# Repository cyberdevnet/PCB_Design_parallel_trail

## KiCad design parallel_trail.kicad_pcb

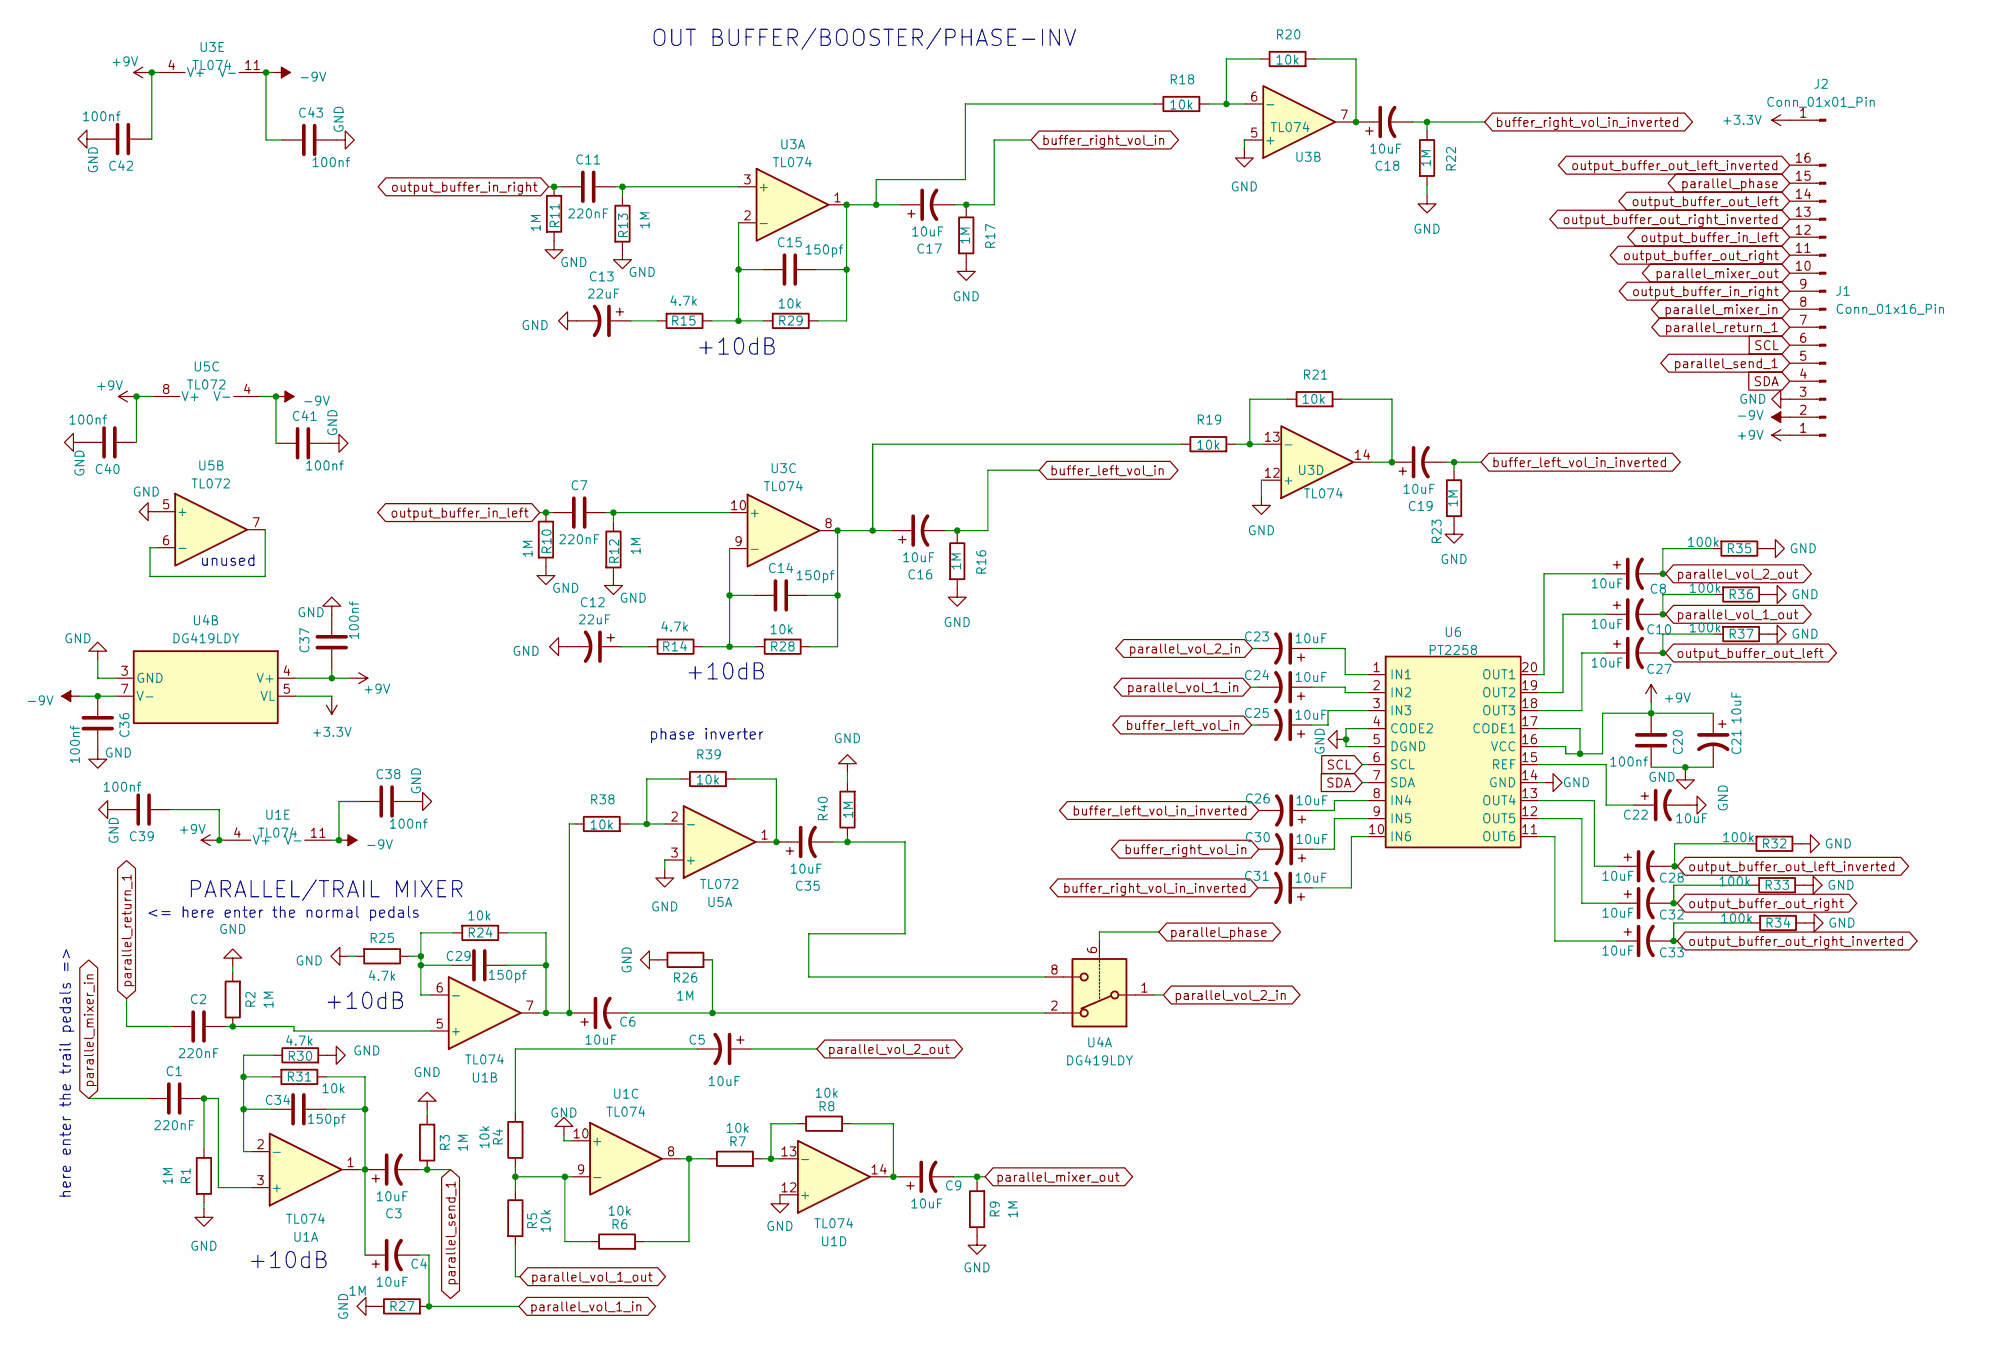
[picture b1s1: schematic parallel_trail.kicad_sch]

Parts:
C1, C2, C7, C11: 220nF; C_0805_2012Metric
C3, C4, C5, C6, C8, C9, C10, C16, C17, C18, C19, C21, C22, C23, C24, C25, C26, C27, C28, C30, C31, C32, C33, C35: 10uF; C_0805_2012Metric
C12, C13: 22uF; C_Elec_6.3x5.4
C14, C15, C29, C34: 150pf; C_0805_2012Metric
C20, C36, C37, C38, C39, C40, C41, C42, C43: 100nf; C_0805_2012Metric
J1: Conn_01x16_Pin; PinHeader_2x08_P2.54mm_Vertical
J2: Conn_01x01_Pin; PinHeader_1x01_P1.00mm_Vertical
R1, R2, R3, R9, R10, R11, R12, R13, R16, R17, R22, R23, R26, R27, R40: 1M; R_0805_2012Metric
R4, R5, R6, R7, R8, R18, R19, R20, R21, R24, R28, R29, R31, R38, R39: 10k; R_0805_2012Metric
R14, R15, R25, R30: 4.7k; R_0805_2012Metric
R32, R33, R34, R35, R36, R37: 100k; R_0805_2012Metric
U1, U3: TL074; SO-14_3.9x8.65mm_P1.27mm
U4: DG419LDY; SOIC-8_3.9x4.9mm_P1.27mm
U5: TL072; SO-8_3.9x4.9mm_P1.27mm
U6: PT2258; SOP-20_7.5x12.8mm_P1.27mm

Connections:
+3.3V: J2.1, U4.5 (VL)
+9V: C20.2, C21.1, C37.2, C39.2, C40.2, C42.2, J1.1, U1.4 (V+), U3.4 (V+), U4.4 (V+), U5.8 (V+), U6.16 (VCC), U6.17 (CODE1)
-9V: C36.2, C38.2, C41.2, C43.2, J1.2, U1.11 (V-), U3.11 (V-), U4.7 (V-), U5.4 (V-)
GND: C12.2, C13.2, C20.1, C21.2, C22.2, C36.1, C37.1, C38.1, C39.1, C40.1, C41.1, C42.1, C43.1, J1.3, R1.2, R2.2, R3.2, R9.1, R10.2, R11.2, R12.2, R13.2, R16.2, R17.2, R22.2, R23.2, R25.2, R26.1, R27.1, R30.2, R32.1, R33.1, R34.1, R35.1, R36.1, R37.1, R40.2, U1.10 (+), U1.12 (+), U3.5 (+), U3.12 (+), U4.3 (GND), U5.3 (+), U5.5 (+), U6.4 (CODE2), U6.5 (DGND), U6.14 (GND)
unnamed: C3.1, C4.1, C34.1, R31.1, U1.1
unnamed: C5.2, R4.2
unnamed: C6.2, R26.2, U4.2
unnamed: C9.1, R8.2, U1.14
unnamed: C12.1, R14.2
unnamed: C13.1, R15.2
unnamed: C14.1, C16.1, R19.1, R28.1, U3.8
unnamed: C15.1, C17.1, R18.1, R29.1, U3.1
unnamed: C18.1, R20.2, U3.7
unnamed: C19.1, R21.2, U3.14
unnamed: C6.1, C29.1, R24.1, R38.1, U1.7
unnamed: C35.1, R39.2, U5.1
unnamed: C35.2, R40.1, U4.8
unnamed: R6.2, R7.1, U1.8
unnamed: C1.1, R1.1, U1.3 (+)
unnamed: C34.2, R30.1, R31.2, U1.2 (-)
unnamed: C2.1, R2.1, U1.5 (+)
unnamed: C29.2, R24.2, R25.1, U1.6 (-)
unnamed: R4.1, R5.1, R6.1, U1.9 (-)
unnamed: R7.2, R8.1, U1.13 (-)
unnamed: C11.1, R13.1, U3.3 (+)
unnamed: C15.2, R15.1, R29.2, U3.2 (-)
unnamed: R18.2, R20.1, U3.6 (-)
unnamed: C7.1, R12.1, U3.10 (+)
unnamed: C14.2, R14.1, R28.2, U3.9 (-)
unnamed: R19.2, R21.1, U3.13 (-)
unnamed: R38.2, R39.1, U5.2 (-)
unnamed: U5.6 (-), U5.7
unnamed: C23.1, U6.1 (IN1)
unnamed: C24.1, U6.2 (IN2)
unnamed: C25.1, U6.3 (IN3)
unnamed: C26.1, U6.8 (IN4)
unnamed: C30.1, U6.9 (IN5)
unnamed: C31.1, U6.10 (IN6)
unnamed: C8.1, U6.20 (OUT1)
unnamed: C10.1, U6.19 (OUT2)
unnamed: C27.1, U6.18 (OUT3)
unnamed: C28.1, U6.13 (OUT4)
unnamed: C32.1, U6.12 (OUT5)
unnamed: C33.1, U6.11 (OUT6)
unnamed: C22.1, U6.15 (REF)
SCL: J1.6, U6.6 (SCL)
SDA: J1.4, U6.7 (SDA)
buffer_left_vol_in: C16.2, C25.2, R16.1
buffer_left_vol_in_inverted: C19.2, C26.2, R23.1
buffer_right_vol_in: C17.2, C30.2, R17.1
buffer_right_vol_in_inverted: C18.2, C31.2, R22.1
output_buffer_in_left: C7.2, J1.12, R10.1
output_buffer_in_right: C11.2, J1.9, R11.1
output_buffer_out_left: C27.2, J1.14, R37.2
output_buffer_out_left_inverted: C28.2, J1.16, R32.2
output_buffer_out_right: C32.2, J1.11, R33.2
output_buffer_out_right_inverted: C33.2, J1.13, R34.2
parallel_mixer_in: C1.2, J1.8
parallel_mixer_out: C9.2, J1.10, R9.2
parallel_phase: J1.15, U4.6
parallel_return_1: C2.2, J1.7
parallel_send_1: C3.2, J1.5, R3.1
parallel_vol_1_in: C4.2, C24.2, R27.2
parallel_vol_1_out: C10.2, R5.2, R36.2
parallel_vol_2_in: C23.2, U4.1
parallel_vol_2_out: C5.1, C8.2, R35.2

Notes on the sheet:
here enter the trail pedals =>
+10dB
unused
phase inverter
PARALLEL/TRAIL MIXER
<= here enter the normal pedals
OUT BUFFER/BOOSTER/PHASE-INV

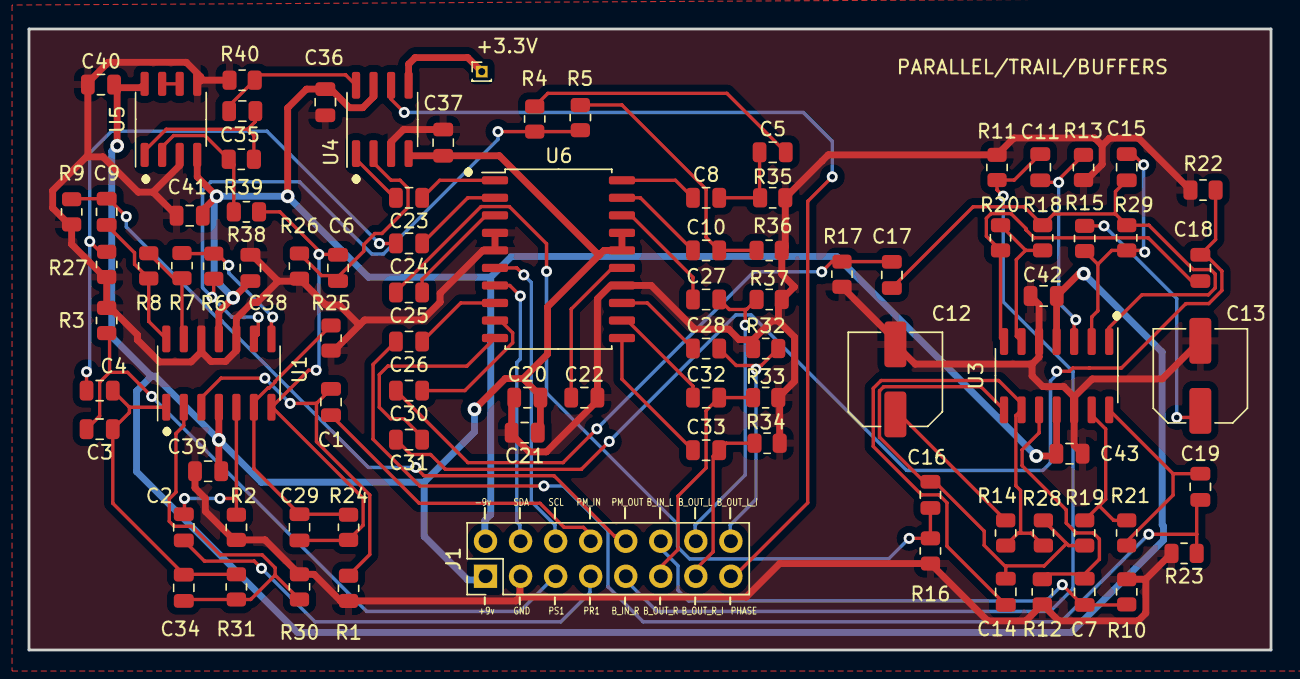
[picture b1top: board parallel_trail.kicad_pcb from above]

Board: 2 copper layers, 90.0 x 45.0 mm, 90 parts (0 on the bottom side), 66 nets.

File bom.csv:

"Id";"Designator";"Footprint";"Quantity";"Designation";"Supplier and ref";
1;"REF**";"PinHeader_2x08_P2.54mm_Vertical";1;"PinHeader_2x08_P2.54mm_Vertical";;;
2;"U6";"SOP-20_7.5x12.8mm_P1.27mm";1;"PT2258";;;
3;"U3,U1";"SO-14_3.9x8.65mm_P1.27mm";2;"TL074";;;
4;"R37,R36,R35,R34,R33,R32";"R_0805_2012Metric";6;"100k";;;
5;"R31,R29,R28,R24,R21,R20,R19,R18,R8,R7,R6,R5,R4";"R_0805_2012Metric";13;"10k";;;
6;"R30,R25,R15,R14";"R_0805_2012Metric";4;"4.7k";;;
7;"R27,R26,R23,R22,R17,R16,R13,R12,R11,R10,R9,R3,R2,R1";"R_0805_2012Metric";14;"1M";;;
8;"C34,C29,C15,C14";"C_0805_2012Metric";4;"150pf";;;
9;"C33,C32,C31,C30,C28,C27,C26,C25,C24,C23,C22,C21,C19,C18,C17,C16,C10,C9,C8,C6,C5,C4,C3";"C_Elec_4x5.4";23;"10uF";;;
10;"C20";"C_0805_2012Metric";1;"100nf";;;
11;"C13,C12";"C_Elec_4x5.4";2;"22uF";;;
12;"C11,C7,C2,C1";"C_0805_2012Metric";4;"220nF";;;

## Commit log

2024-02-16 all new
2024-02-17 added phase switch and rerouted
2024-02-17 add +5 volt pin
2024-02-17 add new plots
2024-03-01 new web bom
2024-03-01 changed dg419 to 3.3V
2024-03-01 add 3.3v label
